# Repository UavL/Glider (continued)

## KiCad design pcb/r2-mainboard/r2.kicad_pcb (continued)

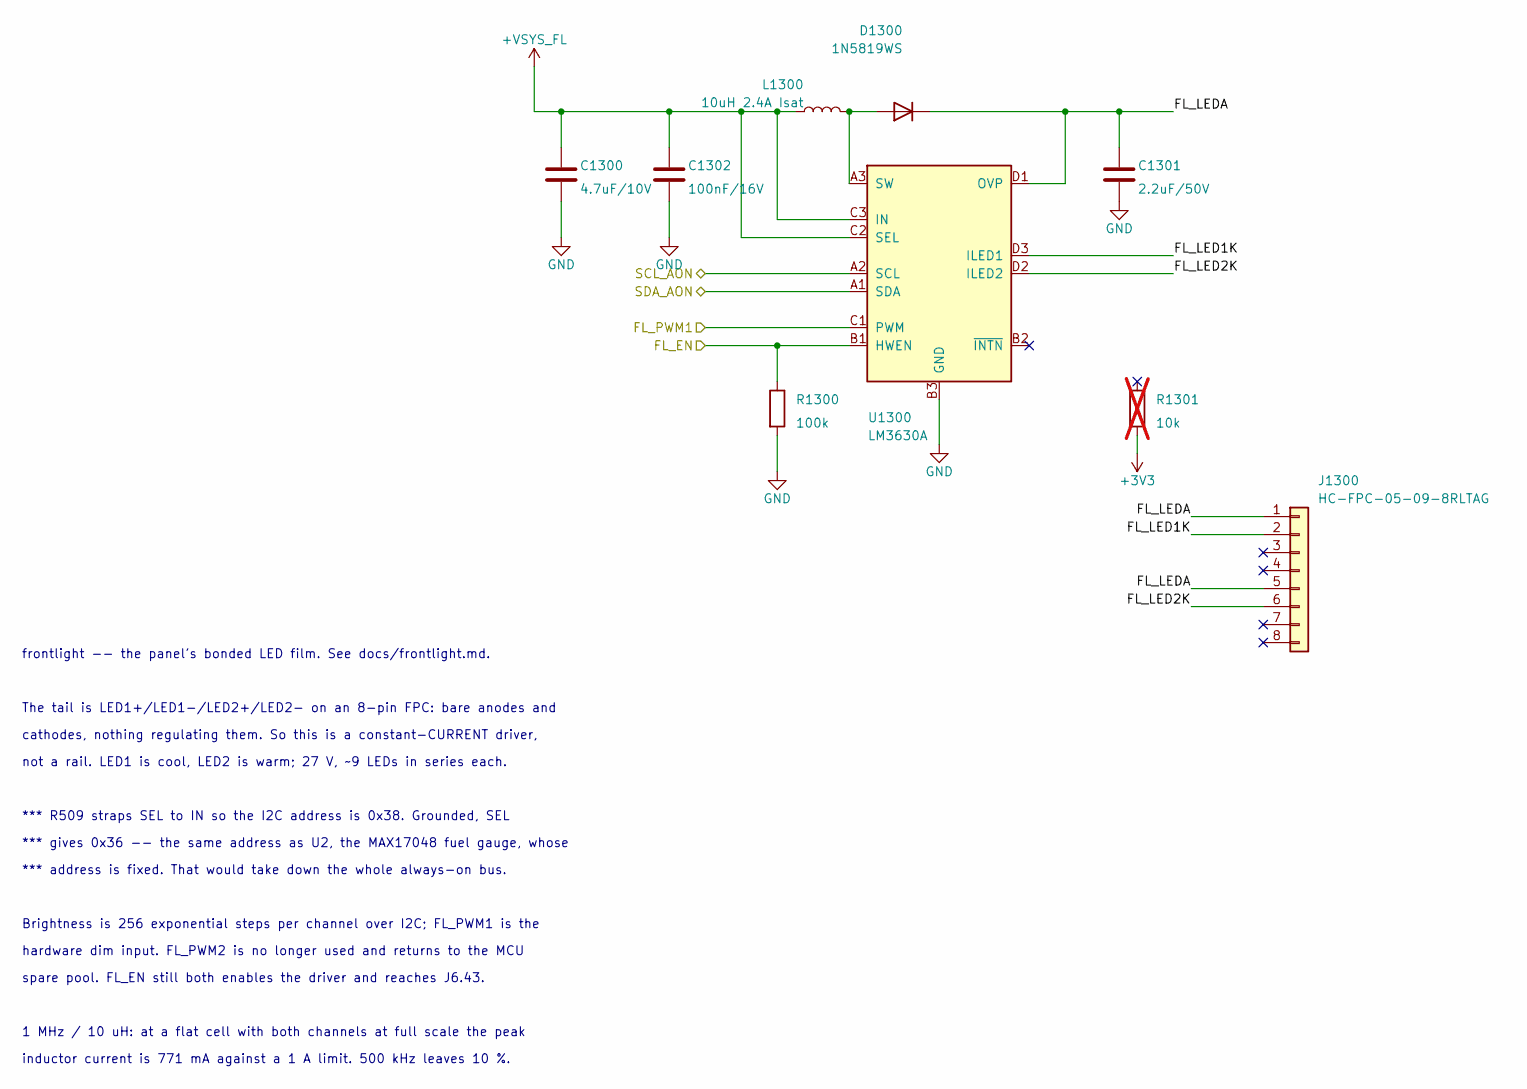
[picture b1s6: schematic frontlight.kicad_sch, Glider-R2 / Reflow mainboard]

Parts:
C1300: 4.7uF/10V; C_0603_1608Metric
C1301: 2.2uF/50V; C_0805_2012Metric
C1302: 100nF/16V; C_0402_1005Metric
D1300: 1N5819WS; D_SOD-323_Alt; MPN B5819WS; LCSC C488405
J1300: HC-FPC-05-09-8RLTAG; HC-FPC-05-09-8RLTAG_Mirrored; MPN HC-FPC-05-09-8RLTAG; LCSC C5213749
L1300: 10uH 2.4A Isat; L_Changjiang_FNR4030S; MPN FNR4030S100MT; LCSC C167879
R1300: 100k; R_0402_1005Metric
R1301: 10k; R_0402_1005Metric; not fitted
U1300: LM3630A; Texas_YFQ0012_DSBGA-12_1.91x1.39mm_Layout3x4_P0.4mm; MPN LM3630ATMX; LCSC C2678552

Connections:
+VSYS_FL: C1300.1, C1302.1, L1300.1, U1300.C2 (SEL), U1300.C3 (IN); also elsewhere on the board
/FL_EN: R1300.1, U1300.B1 (HWEN); also elsewhere on the board
/FL_PWM1: U1300.C1 (PWM); also elsewhere on the board
/SCL_AON: U1300.A2 (SCL); also elsewhere on the board
/SDA_AON: U1300.A1 (SDA); also elsewhere on the board
/frontlight/FL_LED1K: J1300.2, U1300.D3 (ILED1)
/frontlight/FL_LED2K: J1300.6, U1300.D2 (ILED2)
/frontlight/FL_LEDA: C1301.1, D1300.1 (K), J1300.1, J1300.5, U1300.D1 (OVP)
GND: C1300.2, C1301.2, C1302.2, R1300.2, U1300.B3 (GND); also elsewhere on the board
unnamed: D1300.2 (A), L1300.2, U1300.A3 (SW)

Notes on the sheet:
Brightness is 256 exponential steps per channel over I2C; FL_PWM1 is the
spare pool. FL_EN still both enables the driver and reaches J6.43.
cathodes, nothing regulating them. So this is a constant-CURRENT driver,
hardware dim input. FL_PWM2 is no longer used and returns to the MCU
*** address is fixed. That would take down the whole always-on bus.
1 MHz / 10 uH: at a flat cell with both channels at full scale the peak
*** R509 straps SEL to IN so the I2C address is 0x38. Grounded, SEL
The tail is LED1+/LED1-/LED2+/LED2- on an 8-pin FPC: bare anodes and
*** gives 0x36 -- the same address as U2, the MAX17048 fuel gauge, whose
not a rail. LED1 is cool, LED2 is warm; 27 V, ~9 LEDs in series each.
frontlight -- the panel's bonded LED film. See docs/frontlight.md.
inductor current is 771 mA against a 1 A limit. 500 kHz leaves 10 %.

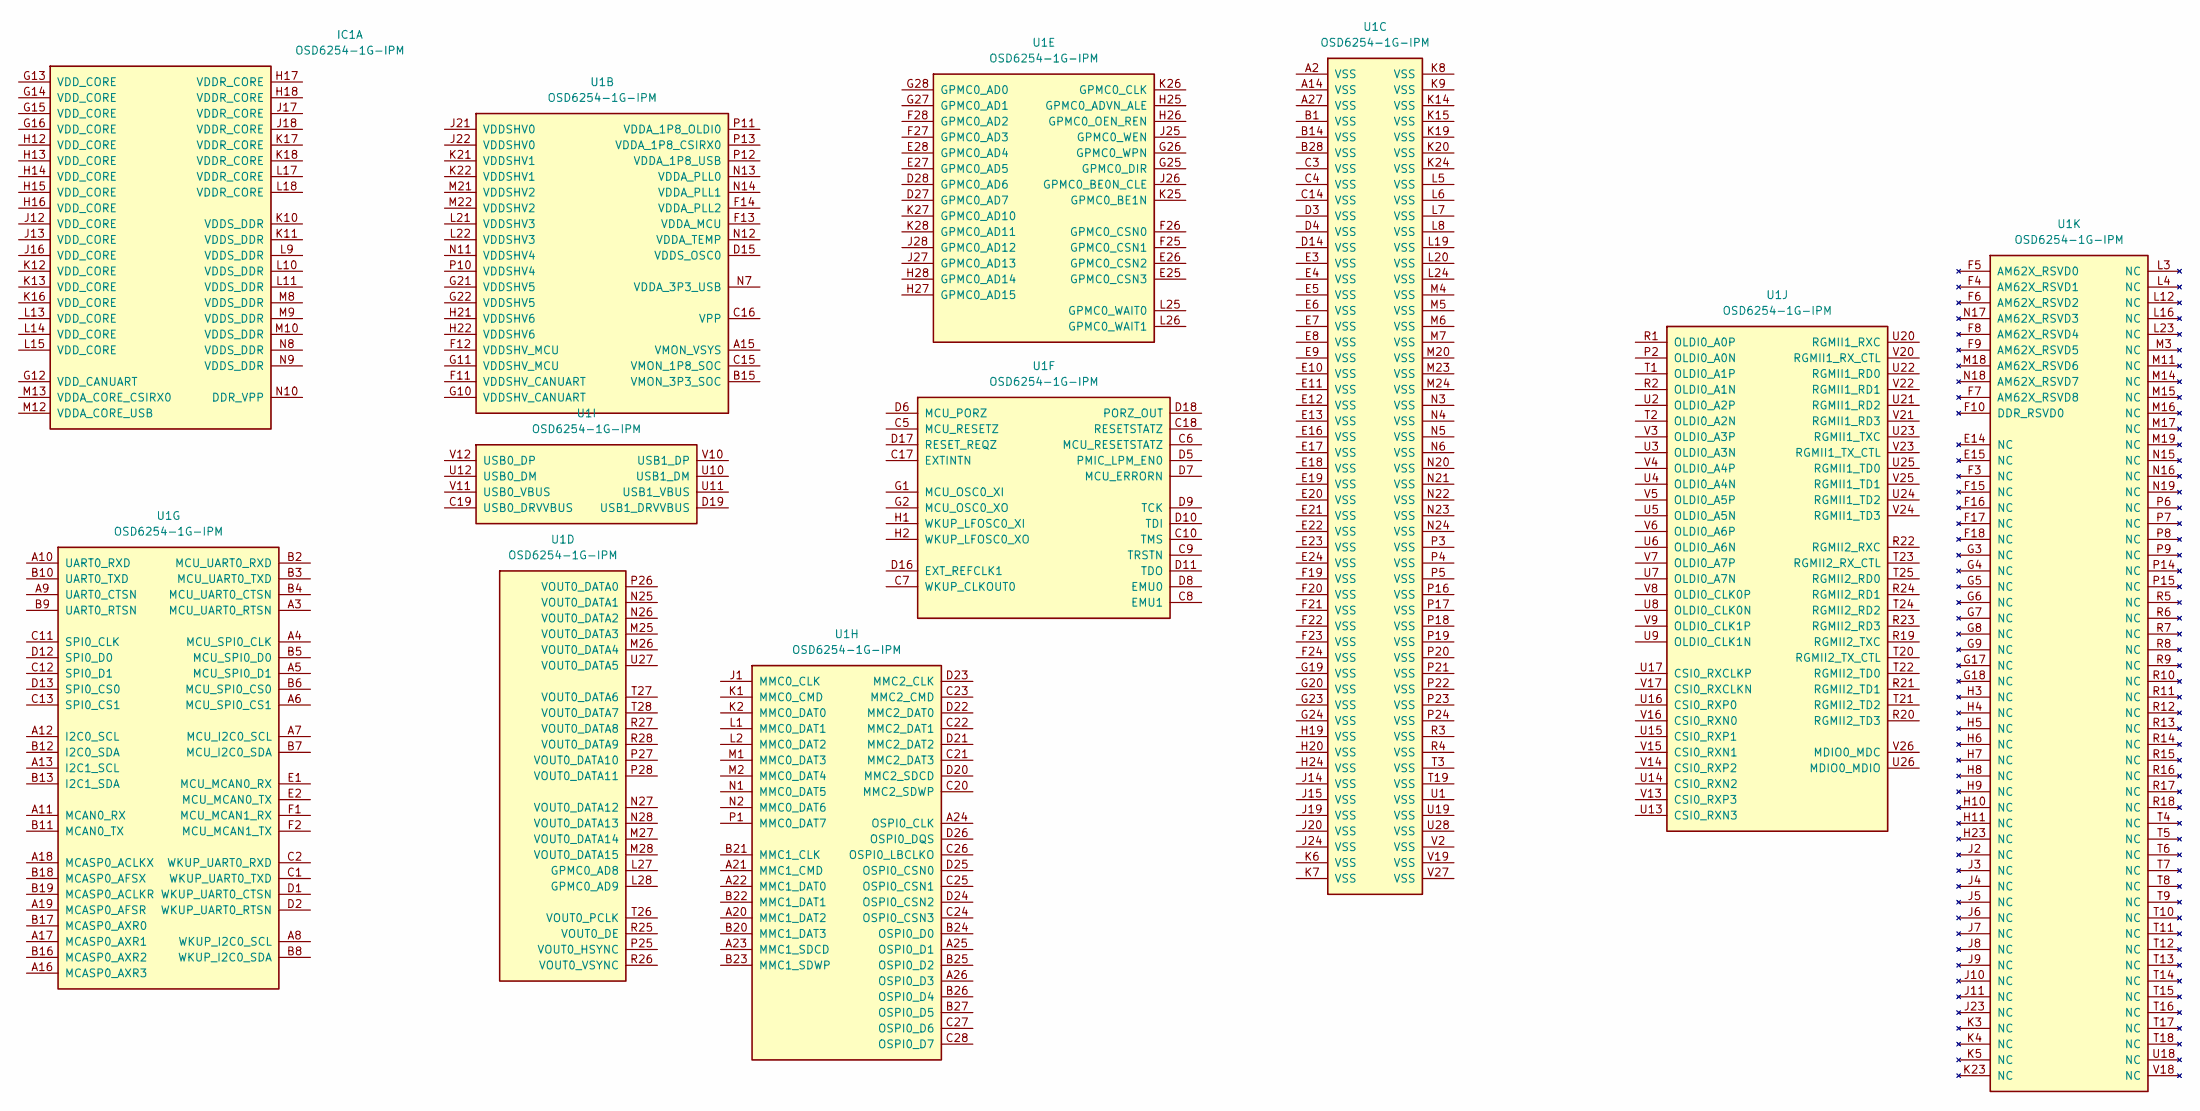
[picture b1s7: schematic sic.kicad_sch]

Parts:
IC1: OSD6254-1G-IPM; BGA500C50P28X18_1400X900X130; Manufacturer_Part_Number OSD6254-1G-IPM
U1: OSD6254-1G-IPM; BGA500C50P28X18_1400X900X130; Manufacturer_Part_Number OSD6254-1G-IPM

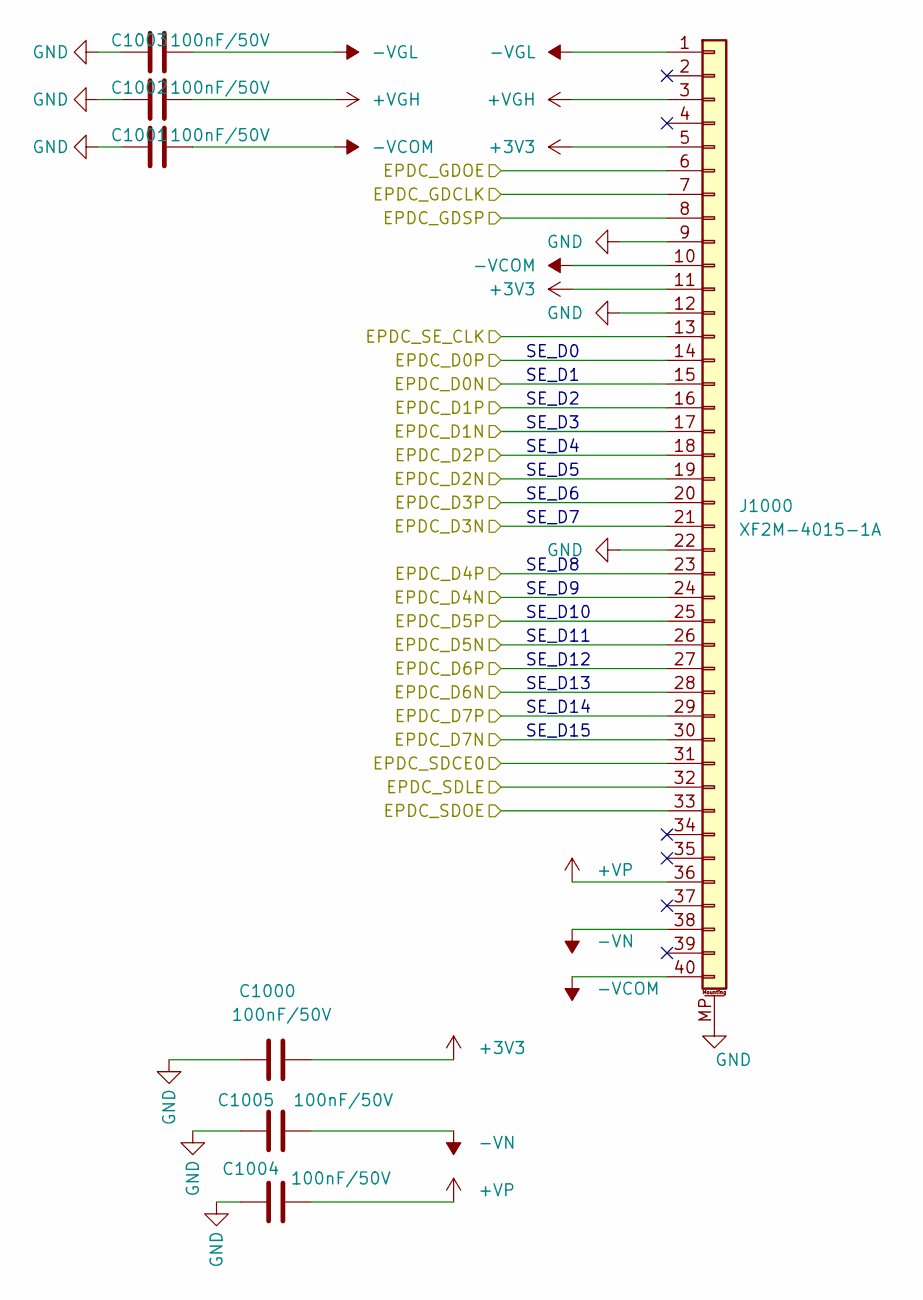
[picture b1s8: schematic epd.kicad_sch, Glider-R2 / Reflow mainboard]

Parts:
C1000, C1001, C1002, C1003, C1004, C1005: 100nF/50V; C_0402_1005Metric; MPN CC0402KRX7R9BB104; LCSC C131394
J1000: XF2M-4015-1A; Omron_XF2M-4015-1A_1x40-1MP_P0.5mm_Horizontal_Mirrored; MPN XF2M-4015-1A; LCSC C225713

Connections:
+3V3: C1000.1, J1000.5, J1000.11; also elsewhere on the board
+VGH: C1002.1, J1000.3; also elsewhere on the board
+VP: C1004.1, J1000.36; also elsewhere on the board
-VCOM: C1001.1, J1000.10, J1000.40; also elsewhere on the board
-VGL: C1003.1, J1000.1; also elsewhere on the board
-VN: C1005.1, J1000.38; also elsewhere on the board
/EPDC_D0N: J1000.15; also elsewhere on the board
/EPDC_D0P: J1000.14; also elsewhere on the board
/EPDC_D1N: J1000.17; also elsewhere on the board
/EPDC_D1P: J1000.16; also elsewhere on the board
/EPDC_D2N: J1000.19; also elsewhere on the board
/EPDC_D2P: J1000.18; also elsewhere on the board
/EPDC_D3N: J1000.21; also elsewhere on the board
/EPDC_D3P: J1000.20; also elsewhere on the board
/EPDC_D4N: J1000.24; also elsewhere on the board
/EPDC_D4P: J1000.23; also elsewhere on the board
/EPDC_D5N: J1000.26; also elsewhere on the board
/EPDC_D5P: J1000.25; also elsewhere on the board
/EPDC_D6N: J1000.28; also elsewhere on the board
/EPDC_D6P: J1000.27; also elsewhere on the board
/EPDC_D7N: J1000.30; also elsewhere on the board
/EPDC_D7P: J1000.29; also elsewhere on the board
/EPDC_GDCLK: J1000.7; also elsewhere on the board
/EPDC_GDOE: J1000.6; also elsewhere on the board
/EPDC_GDSP: J1000.8; also elsewhere on the board
/EPDC_SDCE0: J1000.31; also elsewhere on the board
/EPDC_SDLE: J1000.32; also elsewhere on the board
/EPDC_SDOE: J1000.33; also elsewhere on the board
/EPDC_SE_CLK: J1000.13; also elsewhere on the board
GND: C1000.2, C1001.2, C1002.2, C1003.2, C1004.2, C1005.2, J1000.9, J1000.12, J1000.22, J1000.MP (MountPin); also elsewhere on the board

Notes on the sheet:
SE_D0
SE_D13
SE_D8
SE_D14
SE_D11
SE_D9
SE_D10
SE_D5
SE_D1
SE_D7
SE_D12
SE_D3
SE_D4
SE_D6
SE_D15
SE_D2

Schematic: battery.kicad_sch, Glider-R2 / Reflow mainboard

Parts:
C200: 1uF/25V; C_0402_1005Metric
C201: 8.2uF/25V; C_0805_2012Metric
C202: 47nF/25V; C_0402_1005Metric
C203, C204, C206: 10uF/10V; C_0402_1005Metric
C205: 4.7uF/16V; C_0603_1608Metric
C207: 100nF/16V; C_0402_1005Metric
D200: LED green; LED_0603_1608Metric
F200: 1.5A hold; R_1206_3216Metric
J200: USB-C 16P; USB_C_Receptacle_HRO_TYPE-C-31-M-12; MPN TYPE-C-31-M-12; LCSC C165948
J201: Pico-Lock 504050-0391; Molex_Pico-Lock_504050-0391_1x03-1MP_P1.50mm_Horizontal
J202: SolderPads 3x; SolderPads_1x03_P3.50mm_Wire
L200: 1uH/3A; L_Taiyo-Yuden_NR-30xx
R200, R201: 5.1k; R_0402_1005Metric
R202, R203, R204, R215, R217: 10k; R_0402_1005Metric
R205, R206: 2.2k; R_0402_1005Metric
R207: 260R/1%; R_0402_1005Metric
R208: 5.23k/1%; R_0402_1005Metric
R209: 30.1k/1%; R_0402_1005Metric
R210: 0R; R_0402_1005Metric; not fitted
R211, R212: 100k/1%; R_0402_1005Metric
R213, R214: 100k; R_0402_1005Metric
R216: 1k; R_0402_1005Metric
U200: BQ25892RTW; Texas_RTW_WQFN-24-1EP_4x4mm_P0.5mm_EP2.7x2.7mm_ThermalVias; MPN BQ25892RTWR; LCSC C165480
U201: MAX17048G+T10; TDFN-8-1EP_2x2mm_P0.5mm_EP0.8x1.2mm; MPN MAX17048G+T10; LCSC C2682616
U202: USBLC6-2SC6; SOT-23-6; MPN USBLC6-2SC6; LCSC C7519

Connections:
+3V3_AON: R202.1, R203.1, R204.1, R205.1, R206.1, R215.1, R216.1; also elsewhere on the board
+VBAT: C206.1, C207.1, J201.1, J202.1, U200.13 (BAT), U200.14 (BAT), U201.2 (CELL), U201.3 (VDD)
+VBUS: C200.2, F200.2, R211.1, U200.1 (VBUS), U202.5 (VBUS); also elsewhere on the board
+VSYS: C203.1, C204.1, L200.2, U200.15 (SYS), U200.16 (SYS); also elsewhere on the board
/CHG_CE#: R213.1, U200.9 (~CE); also elsewhere on the board
/CHG_INT#: R204.2, U200.7 (~INT); also elsewhere on the board
/CHG_OTG: R214.1, U200.8 (OTG); also elsewhere on the board
/CHG_PG#: R202.2, U200.3 (~PG); also elsewhere on the board
/CHG_QON#: U200.12 (~QON); also elsewhere on the board
/CHG_STAT#: D200.1 (K), R203.2, U200.4 (STAT); also elsewhere on the board
/GAUGE_ALRT#: R215.2, U201.5 (~ALRT); also elsewhere on the board
/SCL_AON: R206.2, U200.5 (SCL), U201.7 (SCL); also elsewhere on the board
/SDA_AON: R205.2, U200.6 (SDA), U201.8 (SDA); also elsewhere on the board
/USBD+: J200.A6 (USBD+), J200.B6 (USBD+), U202.3 (I/O2), U202.4 (I/O2); also elsewhere on the board
/USBD-: J200.A7 (USBD-), J200.B7 (USBD-), U202.1 (I/O1), U202.6 (I/O1); also elsewhere on the board
/VBUS_DET: R211.2, R212.1; also elsewhere on the board
/battery/+VBUS_PRE: F200.1, J200.A4 (VBUS), J200.A9 (VBUS), J200.B4 (VBUS), J200.B9 (VBUS)
/battery/CHG_PSEL: R210.1, R217.2, U200.2 (PSEL)
/battery/CHG_SW: C202.2, L200.1, U200.19 (SW), U200.20 (SW)
/battery/CHG_TS: J201.2, J202.2, R208.2, R209.1, U200.11 (TS)
/battery/REGN: C205.1, R208.1, R217.1, U200.22 (REGN)
/battery/USB_CC1: J200.A5 (CC1), R200.1
/battery/USB_CC2: J200.B5 (CC2), R201.1
GND: C200.1, C201.1, C203.2, C204.2, C205.2, C206.2, C207.2, J200.A1 (GND), J200.A12 (GND), J200.B1 (GND), J200.B12 (GND), J200.SH (SHIELD), J201.3, J202.3, R200.2, R201.2, R207.2, R209.2, R210.2, R212.2, R213.2, R214.2, U200.17 (PGND), U200.18 (PGND), U200.25 (PGND), U201.1 (CTG), U201.4 (GND), U201.6 (QSTRT), U201.9 (EP), U202.2 (GND); also elsewhere on the board
unnamed: D200.2 (A), R216.2
unnamed: C202.1, U200.21 (BTST)
unnamed: R207.1, U200.10 (ILIM)
unnamed: C201.2, U200.23 (PMID)

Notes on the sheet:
1S cell, 5000 mAh, with pack NTC
*** The PL706090 ships with a JST 1.25 mm plug rated 1 A against ~2 A of
USB-C — charge input and USB2 device port
Charge indicator - lit while STAT is low.
Fuel gauge — MAX17048, I2C 0x36
Defaults while the MCU is unpowered: charging enabled, boost off
right-angle. Replaces a JST-PH that was 2 A and ~6.0 mm tall.
PSEL high = USB host source
ERC power flags — drop the +3V3_AON flag once
J2 Pico-Lock 504050-0391: 3.5 A/contact, 2.00 mm mated, positive lock,
No NTC in pack -> fit 7.68k/10k instead.
J25 bare copper pads, for soldering the cell's leads directly.
TS: 103AT NTC in the pack. RT1/RT2 solved from
power.kicad_sch sources that rail.
Cell attachment -- J2 or J25, same three nets, fit either or both.
*** charge current, so the pack must be re-terminated. battery.md §9.1.
Pull-ups to +3V3_AON (always-on domain)
Charger with power path — BQ25892
to other sheets
V(T1) 73.25% and V(T5) 34.375% of REGN.
STAT
USB-C sink: 5.1k Rd on each CC, separately
VBUS presence, 2.5 V at 5 V in
Fit R38 or R11, never both.

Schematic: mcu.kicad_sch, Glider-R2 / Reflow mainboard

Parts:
C400: 4.7uF/10V; C_0402_1005Metric
C401, C403, C404, C407, C408, C409: 100nF/16V; C_0402_1005Metric
C402: 1uF/16V; C_0402_1005Metric
C405, C406: 18pF/50V; C_0402_1005Metric; MPN CC0402JRNPO9BN180
D400: GREEN; LED_0603_1608Metric; MPN LTST-C191KGKT; LCSC C125098
FB400: 120R@100M; L_0402_1005Metric; MPN BLM15AG121SN1D; LCSC C85812
J400: SWD+JTAG (DNP); PinSocket_2x06_P1.27mm_Vertical_SMD; not fitted
Q400: AO3400A; SOT-23; MPN AO3400A; LCSC C347475
R400: 10k; R_0402_1005Metric
R401, R404, R405: 1k; R_0402_1005Metric
R402, R403: 100k; R_0402_1005Metric
R406: 100k; R_0402_1005Metric; MPN 0402WGF1003TCE; LCSC C25741
R407: 1k; R_0402_1005Metric; MPN 0402WGF1001TCE; LCSC C11702
R408: 1M; R_0402_1005Metric; MPN 0402WGF1004TCE; LCSC C26083
SW400: EVQPUC02K; Panasonic_EVQPUL_EVQPUC
SW401, SW402: SW; SW_SPST_Panasonic_EVQPL_3PL_5PL_PT_A15; MPN EVQPLHA15; LCSC C79172
U400: STM32G0B1RCT6; LQFP-64_10x10mm_P0.5mm; MPN STM32G0B1RCT6; LCSC C3034735
Y400: 32.768kHz; Crystal_SMD_3215-2Pin_3.2x1.5mm; MPN Q13FC13500004; LCSC C32346

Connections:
+3V3_AON: C400.1, C401.1, D400.1 (K), FB400.1, J400.12, R402.1, R403.1, U400.6 (VBAT), U400.8 (VDD); also elsewhere on the board
/CHG_CE#: U400.55 (PD5); also elsewhere on the board
/CHG_INT#: U400.50 (PD0); also elsewhere on the board
/CHG_OTG: U400.57 (PB3); also elsewhere on the board
/CHG_PG#: U400.52 (PD2); also elsewhere on the board
/CHG_QON#: C409.1, R401.2, SW400.1; also elsewhere on the board
/CHG_STAT#: U400.54 (PD4); also elsewhere on the board
/EPD_POS_EN: U400.28 (PB1); also elsewhere on the board
/EPD_PWR_EN: R405.2; also elsewhere on the board
/EPD_THROT: U400.31 (PB11); also elsewhere on the board
/FL_EN: U400.59 (PB5); also elsewhere on the board
/FL_PWM1: U400.60 (PB6); also elsewhere on the board
/FPGA_DONE: U400.34 (PB14); also elsewhere on the board
/FPGA_INIT: U400.64 (PC10); also elsewhere on the board
/FPGA_PROG#: U400.33 (PB13); also elsewhere on the board
/FPGA_SUSP: U400.35 (PB15); also elsewhere on the board
/FPGA_TCK: J400.1; also elsewhere on the board
/FPGA_TDI: J400.3; also elsewhere on the board
/FPGA_TDO: J400.5; also elsewhere on the board
/FPGA_TMS: J400.7; also elsewhere on the board
/GAUGE_ALRT#: U400.53 (PD3); also elsewhere on the board
/MCU_EN_3V3: U400.11 (PF1); also elsewhere on the board
/MCU_EN_5V: U400.10 (PF0); also elsewhere on the board
/MCU_EN_DDR: U400.14 (PC1); also elsewhere on the board
/MCU_EN_FPGA_CORE: U400.13 (PC0); also elsewhere on the board
/MCU_EN_PEN: U400.49 (PC9)
/MCU_EN_TOUCH: U400.38 (PC6); also elsewhere on the board
/MCU_RXD: U400.42 (PA10/UCPD1_DBCC2); also elsewhere on the board
/MCU_TXD: U400.37 (PA9/UCPD1_DBCC1); also elsewhere on the board
/PEN_INT#: U400.43 (PA9/PA11)
/PEN_RXD: U400.26 (PC5)
/PEN_TXD: U400.25 (PC4)
/PG_1V2: U400.2 (PC12); also elsewhere on the board
/PG_1V5: U400.1 (PC11); also elsewhere on the board
/PG_3V3: U400.3 (PC13); also elsewhere on the board
/PG_SOM: R408.1, U400.48 (PC8); also elsewhere on the board
/SCL_AON: U400.62 (PB8); also elsewhere on the board
/SDA_AON: U400.63 (PB9); also elsewhere on the board
/SOM_IRQ#: U400.58 (PB4); also elsewhere on the board
/SOM_MCU_BOOT0: R407.1; also elsewhere on the board
/SOM_MCU_NRST: Q400.1 (G), R406.1; also elsewhere on the board
/SOM_RESET#: U400.47 (PA15); also elsewhere on the board
/SOM_WAKE#: U400.36 (PA8); also elsewhere on the board
/TOUCH_INT#: U400.41 (PD9); also elsewhere on the board
/TOUCH_RST#: U400.16 (PC3); also elsewhere on the board
/USB1_FAULT#: U400.61 (PB7); also elsewhere on the board
/VBUS_DET: U400.51 (PD1); also elsewhere on the board
/VBUS_MEA: U400.24 (PA7); also elsewhere on the board
/VCOM_DAC: U400.21 (PA4); also elsewhere on the board
/VCOM_EN: U400.29 (PB2); also elsewhere on the board
/VCOM_MEA: U400.23 (PA6); also elsewhere on the board
/VCOM_MEA_EN: U400.30 (PB10); also elsewhere on the board
/VGH_DAC: U400.22 (PA5); also elsewhere on the board
/VGH_MEA: U400.19 (PA2); also elsewhere on the board
/VGL_MEA: U400.20 (PA3); also elsewhere on the board
/VN_MEA: U400.18 (PA1); also elsewhere on the board
/VP_MEA: U400.17 (PA0); also elsewhere on the board
/mcu/+3V3_VREF: C402.1, C403.1, FB400.2, U400.7 (VREF+)
/mcu/EPD_PWR_EN_MCU: R405.1, U400.27 (PB0)
/mcu/KEY_NEXT#: C408.1, R403.2, SW402.1, U400.40 (PD8)
/mcu/KEY_PREV#: C407.1, R402.2, SW401.1, U400.39 (PC7)
/mcu/LED_STAT#: R404.2, U400.15 (PC2)
/mcu/MCU_NRST: C404.1, J400.10, Q400.3 (D), U400.12 (PF2)
/mcu/MCU_SWCLK: J400.9, R400.1, R407.2, U400.46 (PA14)
/mcu/MCU_SWDIO: J400.11, U400.45 (PA13)
/mcu/OSC32_IN: C405.1, U400.4 (PC14), Y400.1
/mcu/OSC32_OUT: C406.1, U400.5 (PC15), Y400.2
/mcu/QON_SNS: R401.1, U400.56 (PD6)
GND: C400.2, C401.2, C402.2, C403.2, C404.2, C405.2, C406.2, C407.2, C408.2, C409.2, J400.2, J400.4, J400.6, J400.8, Q400.2 (S), R400.2, R406.2, R408.2, SW400.2, SW401.2, SW402.2, U400.9 (VSS); also elsewhere on the board
unnamed: D400.2 (A), R404.1

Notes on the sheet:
J20 is pads only, not fitted. One footprint for both targets:
the far sheet, referenced to the far rail. MCU_TXD is push-pull and a
eMMC. The MCU keeps only FPGA_PROG#/DONE/SUSP, which are power-domain
SW20 shorts CHG_QON# straight to GND — what the charger expects, and the only path that still works with the MCU unpowered:
ships in 12.5 / 9 / 7 pF and the LCSC listing does not say which.
32.768 kHz LSE
PG_SOM bias. mcu.md §5.9
PC10 carries FPGA_INIT: INIT_B low tells a config error from a
VREF+ (7)
below, their own pins: C40/C41 at pin 8, C43/C44 at pin 7.
silent NOR when DONE never arrives. EXTI10 is free for it.
to battery.kicad_sch (I2C also to power_mon)
to fpga_config, som and frontlight
MCU_TXD and MCU_RXD are named from the MCU's point of view. On
page back PC7 / EXTI7
Confirm before layout, and check drive level. docs/mcu.md §9.
SoM -> MCU recovery. mcu.md §5.8
+5V_DCDC. docs/mcu.md §4.
page forward PD8 / EXTI8
VDDA is merged into the VDD pin on STM32G0, so FB20 isolates the ADC
power_mon's U21 drives this net open-drain from CRITICAL, so an
to epd_power.kicad_sch and power_mon.kicad_sch
power PD6 / EXTI6
UART TX idles high, so firmware must release it before cutting
LAYOUT — the caution under that figure asks for these directly at, or
The SoM, not the MCU, drives Caster's CSR bus — Caster/rtl/csr.v is a
land on dies the MCU itself can unpower, and their pull-ups belong on
4-wire SPI slave, and the LUT/OSD data it carries lives on the SoM's
Sheet interface
EPD_PWR_EN series
enabling it drives the buffer output back into the rail. docs/mcu.md §5.2.
over-current trip must win against the MCU. R45 limits that fight to
Reset and SWD
in ship mode the BATFET is off, so with no USB attached +VSYS and therefore +3V3_AON do not exist. QON idles at 4.3 V from a
to power.kicad_sch
SOM_WAKE#, SOM_IRQ#, SOM_RESET# and FPGA_PROG# are open-drain: they
DISABLED (Table 21 note 2). A 15 s hold forces a BATFET reset, so a clean shutdown has to finish well inside 12 s.
booting from the option bytes; R40 makes that unconditional.
gives 18 pF each. Y20's actual CL is NOT verified — Epson FC-135
Figure 15, p.65: 100 nF + 4.7 uF on VDD/VDDA, 100 nF + 1 uF on VREF+.

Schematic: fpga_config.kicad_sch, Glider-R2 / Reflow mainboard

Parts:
C900, C901, C902, C903, C904, C905, C906, C907: 22uF/6.3V; C_0603_1608Metric; MPN CL10A226MQ8NRNC; LCSC C59461
C908, C909, C910, C911: 4.7uF/6.3V; C_0402_1005Metric; MPN CL05A475MQ5NRNC; LCSC C307423
C912, C913, C914, C915, C916, C917, C918: 470nF/25V; C_0402_1005Metric; MPN CGA0402X5R474K250GT; LCSC C6119801
C919: 100nF/16V; C_0402_1005Metric
R900, R901: 5.1K/1%; R_0402_1005Metric; MPN 0402WGF5101TCE; LCSC C25905
R902: 1K/1%; R_0402_1005Metric; MPN 0402WGF1001TCE; LCSC C11702
R903: 33R/1%; R_0402_1005Metric; MPN 0402WGF330JTCE; LCSC C25105
R904, R906, R907: 10k; R_0402_1005Metric
R905: 100R; R_0402_1005Metric
R908: 4.7k; R_0402_1005Metric
U700: XC6SLX-FTG256; Xilinx_FTG256; MPN XC6SLX16-2FTG256C; LCSC C39313
U902: W25Q128JVSIQ; QSPI Flash SOIC; MPN W25Q128JVSIQ; LCSC C97521
X900: 33.33MHz; Oscillator_SMD_Abracon_ASE-4Pin_3.2x2.5mm; MPN 1532H-33.333JWVDTSL; LCSC C46598403

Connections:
+1V5: C900.1, C904.1, C908.1, C912.1, C916.1; also elsewhere on the board
+3V3: C901.1, C902.1, C903.1, C905.1, C906.1, C907.1, C909.1, C910.1, C911.1, C913.1, C914.1, C915.1, C917.1, C918.2, C919.1, R900.1, R902.1, R904.1, R906.1, R907.1, R908.1, U700.N7 (VCCO_2), U700.N10 (VCCO_2), U700.R4 (VCCO_2), U700.R8 (VCCO_2), U700.T11 (IO_L1N_M0_CMPMISO_2), U902.8 (VCC), X900.1 (EN), X900.4 (Vdd); also elsewhere on the board
/FPGA_CLK33: R903.2, U700.M9 (IO_L29P_GCLK3_2); also elsewhere on the board
/FPGA_CS: U700.L10 (IO_L16P_2); also elsewhere on the board
/FPGA_DONE: R902.2, U700.P13 (DONE_2); also elsewhere on the board
/FPGA_INIT: R908.2, U700.R3 (IO_L65P_INIT_B_2); also elsewhere on the board
/FPGA_MISO: U700.T10 (IO_L3N_MOSI_CSI_B_MISO0_2), U902.5 (DI(IO0)); also elsewhere on the board
/FPGA_MOSI: U700.P10 (IO_L3P_D0_DIN_MISO_MISO1_2), U902.2 (DO(IO1)); also elsewhere on the board
/FPGA_PROG#: R900.2, U700.T2 (PROGRAM_B_2); also elsewhere on the board
/FPGA_SCLK: U700.R11 (IO_L1P_CCLK_2), U902.6 (CLK); also elsewhere on the board
/FPGA_SUSP: R901.1, U700.P14 (SUSPEND); also elsewhere on the board
/FPGA_TCK: U700.C14 (TCK); also elsewhere on the board
/FPGA_TDI: U700.C12 (TDI); also elsewhere on the board
/FPGA_TDO: U700.E14 (TDO); also elsewhere on the board
/FPGA_TMS: U700.A15 (TMS); also elsewhere on the board
/NOR_CS: R905.1; also elsewhere on the board
/fpga_config/NOR_CS#: R904.2, R905.2, U700.T3 (IO_L65N_CSO_B_2), U902.1 (~CS)
/fpga_config/NOR_IO2: R906.2, U700.N12 (IO_L12P_D1_MISO2_2), U902.3 (~WP(IO2))
/fpga_config/NOR_IO3: R907.2, U700.P12 (IO_L12N_D2_MISO3_2), U902.7 (~RESET(IO3))
GND: C900.2, C901.2, C902.2, C903.2, C904.2, C905.2, C906.2, C907.2, C908.2, C909.2, C910.2, C911.2, C912.2, C913.2, C914.2, C915.2, C916.2, C917.2, C918.1, C919.2, R901.2, U700.N11 (IO_L13P_M1_2), U902.4 (GND), X900.2 (GND); also elsewhere on the board
unnamed: R903.1, X900.3 (OUT)

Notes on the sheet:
VCCO1
VCCO2
these wires -- see docs/fpga.md for the direction table.
LOOK inverted: FPGA_MOSI is data toward the FPGA, so it
VCCO3
configuring. The net names are host-centric and only
VCCO0
lands on the FPGA's DIN pin and on the NOR's DO, and
Owed in Caster: -g ConfigRate 2 -> 22 (2 makes self-boot 1.9 s, five times
slower than R1's 360-400 ms), -g Binary:no -> yes, and a PULLUP constraint
a gateware change, not a respin. UG380 Fig 2-13; its note 4 requires these
Config NOR -- the FPGA boots itself: master SPI,
pull-ups to VCCO_2, which is why pins 3/7 are no longer tied hard to +3V3.
Nothing changes in x1: the pull-ups hold WP#/HOLD# high as the tie did.
R412/R413 and the two nets to N12/P12 exist so that master-SPI x4 boot is
on N12/P12 so -g UnusedPin:PullDown does not fight R412/R413.
M[1:0]=01 (UG380 Table 2-1), CCLK an output while
FPGA_MISO drives the NOR's DI. Three masters share

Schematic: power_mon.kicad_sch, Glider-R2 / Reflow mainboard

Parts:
C1200: 1nF/50V; C_0402_1005Metric; MPN 0402B102K500NT; LCSC C1523
C1201, C1202, C1203: 100nF/50V; C_0402_1005Metric; MPN CC0402KRX7R9BB104; LCSC C131394
C1204, C1205, C1206, C1207: 1nF/25V; C_0402_1005Metric; MPN 0402B102K500NT; LCSC C1523
R1200, R1209, R1211, R1212, R1214: 1M/1%; R_0402_1005Metric; MPN 0402WGF1004TCE; LCSC C26083
R1201, R1208, R1210, R1213, R1215: 100K/1%; R_0402_1005Metric; MPN 0402WGF1003TCE; LCSC C25741
R1202, R1203, R1204, R1205, R1206, R1207, R1216, R1217: 20mR; R_0805_2012Metric; MPN FRL0805FR020TS; LCSC C7467301
U1200, U1201, U1202: INA3221; Texas_RGV0016A_VQFN-16-1EP_4x4mm_P0.65mm_EP2.1x2.1mm; MPN INA3221AIRGVR; LCSC C181255

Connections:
+1V2_DCDC: R1205.2, U1202.15 (IN+2); also elsewhere on the board
+1V2_FPGA: R1205.1, U1202.14 (IN-2); also elsewhere on the board
+1V5: R1204.1, U1202.11 (IN-1); also elsewhere on the board
+1V5_DCDC: R1204.2, U1202.12 (IN+1); also elsewhere on the board
+3V3: R1206.1, U1200.1 (IN-3); also elsewhere on the board
+3V3_AON: C1201.1, C1202.1, C1203.1, R1213.2, R1215.2, R1217.1, U1200.4 (VS), U1200.16 (VPU), U1201.4 (VS), U1201.5 (A0), U1201.14 (IN-2), U1201.16 (VPU), U1202.4 (VS), U1202.16 (VPU); also elsewhere on the board
+3V3_AON_DCDC: R1217.2, U1201.15 (IN+2); also elsewhere on the board
+3V3_DCDC: R1206.2, U1200.2 (IN+3); also elsewhere on the board
+5V_DCDC: R1216.2, U1201.12 (IN+1); also elsewhere on the board
+5V_EG: R1203.2, U1200.14 (IN-2); also elsewhere on the board
+5V_EPD: R1202.1, R1203.1, U1200.12 (IN+1), U1200.15 (IN+2); also elsewhere on the board
+5V_ES: R1202.2, U1200.11 (IN-1); also elsewhere on the board
+5V_SOM: R1216.1, U1201.11 (IN-1); also elsewhere on the board
+VBUS: R1200.1; also elsewhere on the board
+VGH: R1211.2; also elsewhere on the board
+VP: R1209.2; also elsewhere on the board
+VSYS: R1207.2, U1201.2 (IN+3); also elsewhere on the board
+VSYS_FL: R1207.1, U1201.1 (IN-3); also elsewhere on the board
-VGL: R1214.1; also elsewhere on the board
-VN: R1212.1; also elsewhere on the board
/EPD_PWR_EN: U1200.9 (CRITICAL); also elsewhere on the board
/SCL_AON: U1200.6 (SCL), U1201.6 (SCL), U1202.6 (SCL); also elsewhere on the board
/SDA_AON: U1200.7 (SDA), U1201.7 (SDA), U1202.5 (A0), U1202.7 (SDA); also elsewhere on the board
/VBUS_MEA: C1200.1, R1200.2, R1201.1; also elsewhere on the board
/VGH_MEA: C1205.2, R1210.2, R1211.1; also elsewhere on the board
/VGL_MEA: C1207.2, R1214.2, R1215.1; also elsewhere on the board
/VN_MEA: C1206.2, R1212.2, R1213.1; also elsewhere on the board
/VP_MEA: C1204.2, R1208.2, R1209.1; also elsewhere on the board
GND: C1200.2, C1201.2, C1202.2, C1203.2, C1204.1, C1205.1, C1206.1, C1207.1, R1201.2, R1208.1, R1210.1, U1200.3 (GND), U1200.5 (A0), U1200.17 (EP), U1201.3 (GND), U1201.17 (EP), U1202.1 (IN-3), U1202.2 (IN+3), U1202.3 (GND), U1202.17 (EP); also elsewhere on the board

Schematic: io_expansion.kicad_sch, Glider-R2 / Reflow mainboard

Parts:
C1400: 1uF/16V; C_0402_1005Metric
C1401: 1uF/16V; C_0402_1005Metric; not fitted
C1402, C1404: 100nF/50V; C_0402_1005Metric
C1403: 22uF/10V; C_0805_2012Metric
J1400: HC-FPC-05-09-6RLTAG; MPN HC-FPC-05-09-6RLTAG; LCSC C5213748
J1401: HC-FPC-05-09-6RLTAG; MPN HC-FPC-05-09-6RLTAG; LCSC C5213748; not fitted
J1402: USB-C 16P; USB_C_Receptacle_HRO_TYPE-C-31-M-12; MPN TYPE-C-31-M-12; LCSC C165948
R1400, R1401: 56k; R_0402_1005Metric
R1402: 49.9k/1%; R_0402_1005Metric
R1403: 100k; R_0402_1005Metric
U1400: TPS22914BYFPR; WLCSP-4_0.89x0.89mm_Layout2x2_P0.5mm; MPN TPS22914BYFPR; LCSC C1848394
U1401: TPS22914BYFPR; WLCSP-4_0.89x0.89mm_Layout2x2_P0.5mm; MPN TPS22914BYFPR; LCSC C1848394; not fitted
U1402: TPS2553DBVR; SOT-23-6; MPN TPS2553DBVR; LCSC C55266
U1403: USBLC6-2SC6; SOT-23-6; MPN USBLC6-2SC6; LCSC C7519

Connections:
+3V3: R1403.1, U1400.A2 (IN), U1401.A2 (IN); also elsewhere on the board
+5V_DCDC: C1402.1, R1400.1, R1401.1, U1402.1 (IN); also elsewhere on the board
/MCU_EN_TOUCH: U1400.B2 (ON); also elsewhere on the board
/SCL_AON: J1400.3; also elsewhere on the board
/SDA_AON: J1400.4; also elsewhere on the board
/TOUCH_INT#: J1400.5; also elsewhere on the board
/TOUCH_RST#: J1400.6; also elsewhere on the board
/USB1_D+: J1402.A6 (USBD+), J1402.B6 (USBD+), U1403.3 (I/O2), U1403.4 (I/O2); also elsewhere on the board
/USB1_D-: J1402.A7 (USBD-), J1402.B7 (USBD-), U1403.1 (I/O1), U1403.6 (I/O1); also elsewhere on the board
/USB1_DRVVBUS: U1402.3 (EN); also elsewhere on the board
/USB1_FAULT#: R1403.2, U1402.4 (~FAULT); also elsewhere on the board
/USB1_VBUS: C1403.1, C1404.1, J1402.A4 (VBUS), J1402.A9 (VBUS), J1402.B4 (VBUS), J1402.B9 (VBUS), U1402.6 (OUT), U1403.5 (VBUS); also elsewhere on the board
/io_expansion/+3V3_TOUCH: C1400.1, J1400.1, U1400.A1 (OUT)
GND: C1400.2, C1401.2, C1402.2, C1403.2, C1404.2, J1400.2, J1401.2, J1401.6, J1402.A1 (GND), J1402.A12 (GND), J1402.B1 (GND), J1402.B12 (GND), J1402.SH (SHIELD), R1402.2, U1400.B1 (GND), U1401.B1 (GND), U1402.2 (GND), U1403.2 (GND); also elsewhere on the board
unnamed: C1401.1, J1401.1, U1401.A1 (OUT)
unnamed: J1402.A5 (CC1), R1400.2
unnamed: J1402.B5 (CC2), R1401.2
unnamed: R1402.1, U1402.5 (ILIM)

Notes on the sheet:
*** is the one guess here. Confirm against the real parts before fab, or
are routed, and both gated rails exist. PC4/PC5 are USART3_TX/RX at AF0 --
sits on the existing always-on bus with the charger, gauge and INA3221s.
display + power only, and these get pads so they can be added later.
*** switches, their capacitors. No connector fitted means no load, so a
*** consume none of the thin stock epd-port.md 7 flags.
Intended for external Data storage.
SoM -> Stylus Panel
Host Only USB
Touch Input Panel Driver Circuit
*** the digitizer is chosen -- the panel is not either -- so the pad order
*** accept that this group alone may need a respin. io-expansion.md 5.
Certain, and what stops a whole-board respin: the seven MCU pins exist and
SoM -> Touch Panel (I2C)
the one allocation that is not interchangeable. Touch adds no I2C pins; it
See docs/io-expansion.md. Plan constraint 3: the first board is compute +
io_expansion -- touch and pen, provisioned but NOT FITTED.
Stylus Input Panel Driver Circuit
*** EVERYTHING ON THIS SHEET IS DNP -- both connectors, both load
*** THE FPC PIN ORDER IS PROVISIONAL. Neither the touch controller nor
*** fitted switch would power nothing. It also means these two TPS22914s
